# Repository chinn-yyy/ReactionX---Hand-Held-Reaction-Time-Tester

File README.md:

# ReactionX---Hand-Held-Reaction-Time-Tester
Ever wanted to know your reaction time? Well look no further because this is a reaction time tester! Simply click the button and wait for the red light to turn green.

I was doing some math in class and this kid next to me was on this reaction time tester website. I thought to myself, "could I make that in real life?" As soon as I got home I started researching, now I'm here. When you plug it in, it immediately greets you by saying, "ReactionX" and the highscore. Click start to test. Wait about 3-7 seconds before the LEDs turn from red to green. Once they do click either of the big buttons and it shows how long it took. Click early? Nope! When you click early it greets you with the screen of death, "To early!" 

I designed this as a project for Blueprint by HackClub and I think it turned out great. I used KiCad and Fusion360 to create all of the 3D models and electrical stuff. In total, this project took me about 5-6 hours.

Finally, here are some pictures of the finished result:

Fully Assembled (CAD):

Schematic:

PCB editor:

CAD:

BOM:

| Name:                          | Description:                                                        | $: (each) | Shipping $:                 | Ct: | Manufacturer: | Total $ (w/ tax + shipping): | URL:                                                                                                                                                                                                                                                                                                                                                                                                                                                                                                                                                                                                                                                                  |
|--------------------------------|---------------------------------------------------------------------|-----------|-----------------------------|-----|---------------|------------------------------|-----------------------------------------------------------------------------------------------------------------------------------------------------------------------------------------------------------------------------------------------------------------------------------------------------------------------------------------------------------------------------------------------------------------------------------------------------------------------------------------------------------------------------------------------------------------------------------------------------------------------------------------------------------------------|
| Seeed Studio XIAO RP2040       | Brains of the project, the MCU.                                     | $7.64     | $0.00                       | 1   | AliExpress    | $8.82                        | https://www.aliexpress.us/item/3256807240972277.html?spm=a2g0o.productlist.main.3.5d4a379crVwXcr&algo_pvid=40b24cbb-ccf1-49c9-b14e-7b9223d0d998&algo_exp_id=40b24cbb-ccf1-49c9-b14e-7b9223d0d998-2&pdp_ext_f=%7B%22order%22%3A%2234%22%2C%22eval%22%3A%221%22%2C%22fromPage%22%3A%22search%22%7D&pdp_npi=6%40dis%21USD%217.64%217.64%21%21%217.64%217.64%21%402101c44f17720601246066455e8d6c%2112000040716641980%21sea%21US%216916366760%21X%211%210%21n_tag%3A-29913%3Bd%3A729337c7%3Bm03_new_user%3A-29895&curPageLogUid=Ddu9g5fCrdZE&utparam-url=scene%3Asearch%7Cquery_from%3A%7Cx_object_id%3A1005007427287029%7C_p_origin_prod%3A                               |
| 6x6x6 Tacticle Push Button 12V | 2 pin buttons for clicking. Pack of 20.                             | $1.05     | $0.00                       | 1   | AliExpress    | $1.21                        | https://www.aliexpress.us/item/3256805859865632.html?spm=a2g0o.productlist.main.5.6d74378dUMKjkO&algo_pvid=602265cd-c18e-4c92-9666-59a2cdb82617&algo_exp_id=602265cd-c18e-4c92-9666-59a2cdb82617-4&pdp_ext_f=%7B%22order%22%3A%227215%22%2C%22eval%22%3A%221%22%2C%22fromPage%22%3A%22search%22%7D&pdp_npi=6%40dis%21USD%211.07%211.05%21%21%211.07%211.05%21%40210328db17714519752192151e5a1b%2112000035472972531%21sea%21US%216916366760%21X%211%210%21n_tag%3A-29913%3Bd%3A729337c7%3Bm03_new_user%3A-29895&curPageLogUid=KOWyfwiLLwPj&utparam-url=scene%3Asearch%7Cquery_from%3A%7Cx_object_id%3A1005006046180384%7C_p_origin_prod%3A                             |
| 0.91 inch OLED                 | 0.91 inch, 128x32, SSD1306, I2C, OLED display.                      | $1.97     | $0.00                       | 1   | AliExpress    | $2.27                        | https://www.aliexpress.us/item/3256805114690528.html?spm=a2g0o.productlist.main.33.508byZ3oyZ3oyT&algo_pvid=eb5a6790-e38d-4eb1-b34e-9abb2a502be0&algo_exp_id=eb5a6790-e38d-4eb1-b34e-9abb2a502be0-32&pdp_ext_f=%7B%22order%22%3A%222979%22%2C%22eval%22%3A%221%22%2C%22fromPage%22%3A%22search%22%7D&pdp_npi=6%40dis%21USD%211.97%211.97%21%21%211.97%211.97%21%402103212317713684409616193ef62c%2112000032548039884%21sea%21US%216916366760%21X%211%210%21n_tag%3A-29913%3Bd%3A729337c7%3Bm03_new_user%3A-29895&curPageLogUid=xd4wKAHaNW7A&utparam-url=scene%3Asearch%7Cquery_from%3A%7Cx_object_id%3A1005005301005280%7C_p_origin_prod%3A                           |
| SK6812 MINI-E RGB              | Addressable LEDs to tell you when to click the buttons. Pack of 20. | $2.37     | $0.00                       | 1   | AliExpress    | $2.73                        | https://www.aliexpress.us/item/3256805007401420.html?spm=a2g0o.productlist.main.5.277b37378ad11X&algo_pvid=1e78fde7-5114-430b-8e2b-01034e21220c&algo_exp_id=1e78fde7-5114-430b-8e2b-01034e21220c-4&pdp_ext_f=%7B%22order%22%3A%22354%22%2C%22eval%22%3A%221%22%2C%22fromPage%22%3A%22search%22%7D&pdp_npi=6%40dis%21USD%216.40%216.02%21%21%2143.95%2141.34%21%40210328df17716245048521216e488d%2112000032072424635%21sea%21US%216916366760%21X%211%210%21n_tag%3A-29913%3Bd%3A729337c7%3Bm03_new_user%3A-29895%3BpisId%3A5000000200978327&curPageLogUid=NBaz6TRdqNda&utparam-url=scene%3Asearch%7Cquery_from%3A%7Cx_object_id%3A1005005193716172%7C_p_origin_prod%3A |
| PCB                            | Custom printed circuit board. Pack of 5.                            | $6.60     | $3.30                       | 1   | JLCPCB        | $10.92                       | https://www.jlcpcb.com                                                                                                                                                                                                                                                                                                                                                                                                                                                                                                                                                                                                                                                |
| TOTAL:                         |                                                                     |           | *Ships with switching diode |     |               | $25.95                       | Link to Spreadsheet: https://docs.google.com/spreadsheets/d/1idejGBRncEobSxDtzh-fEDHo9kf2D_G95gO1wz3TeUY/edit?gid=0#gid=0                                                                                                                                                                                                                                                                                                                                                                                                                                                                                                                                             |

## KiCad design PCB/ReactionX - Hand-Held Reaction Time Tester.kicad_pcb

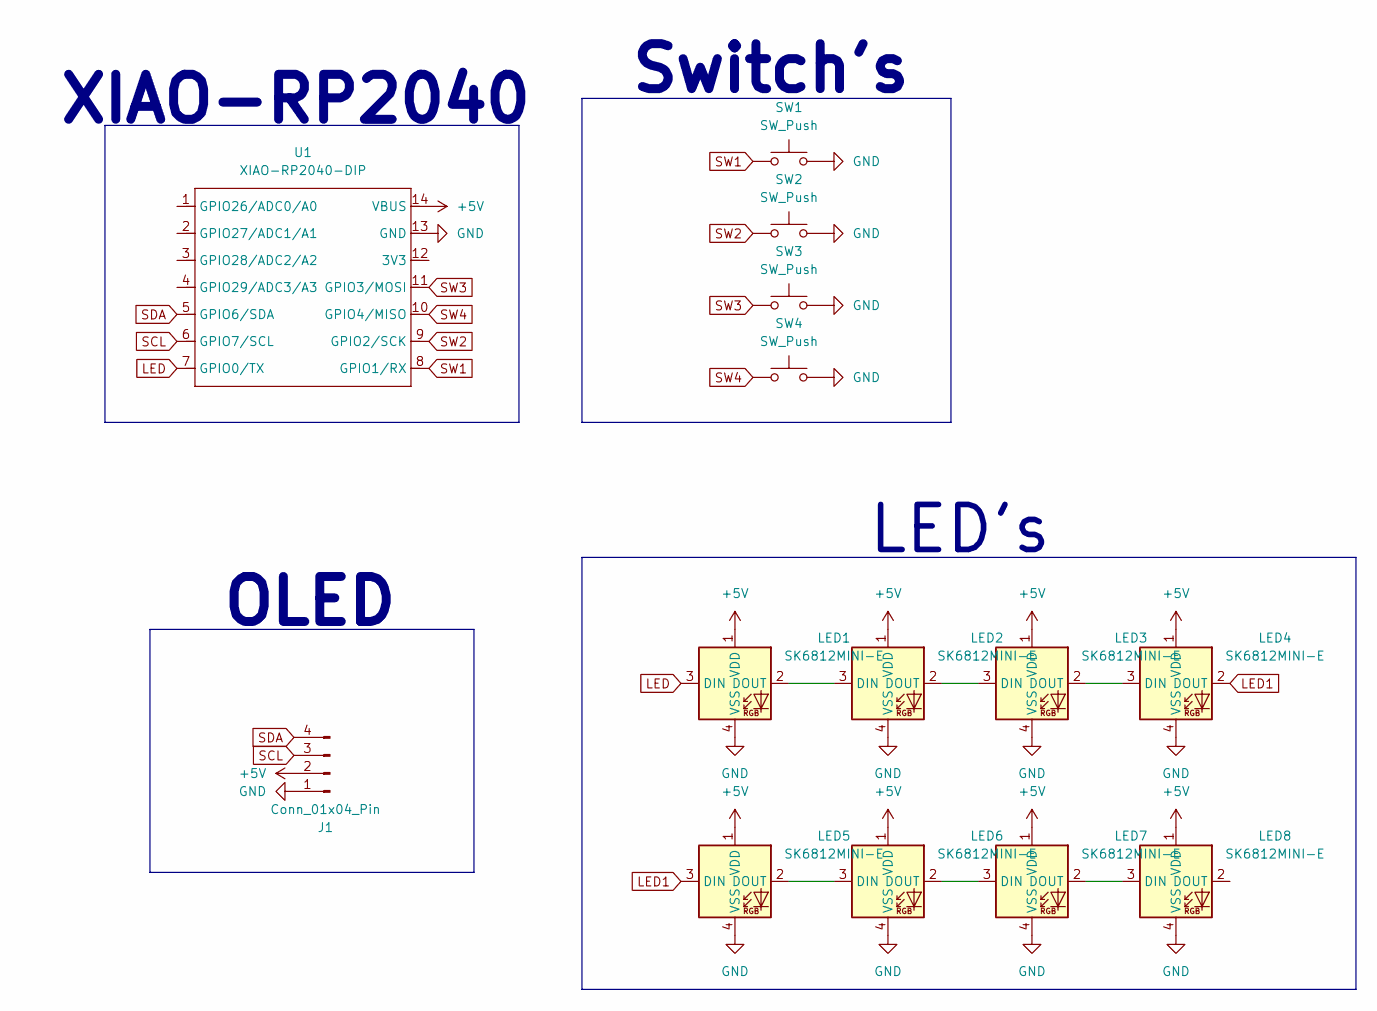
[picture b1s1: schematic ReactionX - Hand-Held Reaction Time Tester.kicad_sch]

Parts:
J1: Conn_01x04_Pin; OLED_0.91_128x32
LED1, LED2, LED3, LED4, LED5, LED6, LED7, LED8: SK6812MINI-E; LED_6028R
SW1, SW2, SW3, SW4: SW_Push; SW_PUSH_6mm_H7.3mm
U1: XIAO-RP2040-DIP

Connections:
+5V: J1.2, LED1.1 (VDD), LED2.1 (VDD), LED3.1 (VDD), LED4.1 (VDD), LED5.1 (VDD), LED6.1 (VDD), LED7.1 (VDD), LED8.1 (VDD), U1.14 (VBUS)
GND: J1.1, LED1.4 (VSS), LED2.4 (VSS), LED3.4 (VSS), LED4.4 (VSS), LED5.4 (VSS), LED6.4 (VSS), LED7.4 (VSS), LED8.4 (VSS), SW1.2, SW2.2, SW3.2, SW4.2, U1.13 (GND)
LED: LED1.3 (DIN), U1.7 (GPIO0/TX)
LED1: LED4.2 (DOUT), LED5.3 (DIN)
unnamed: LED1.2 (DOUT), LED2.3 (DIN)
unnamed: LED2.2 (DOUT), LED3.3 (DIN)
unnamed: LED3.2 (DOUT), LED4.3 (DIN)
unnamed: LED5.2 (DOUT), LED6.3 (DIN)
unnamed: LED6.2 (DOUT), LED7.3 (DIN)
unnamed: LED7.2 (DOUT), LED8.3 (DIN)
SCL: J1.3, U1.6 (GPIO7/SCL)
SDA: J1.4, U1.5 (GPIO6/SDA)
SW1: SW1.1, U1.8 (GPIO1/RX)
SW2: SW2.1, U1.9 (GPIO2/SCK)
SW3: SW3.1, U1.11 (GPIO3/MOSI)
SW4: SW4.1, U1.10 (GPIO4/MISO)

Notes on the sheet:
OLED
XIAO-RP2040
LED's
Switch's

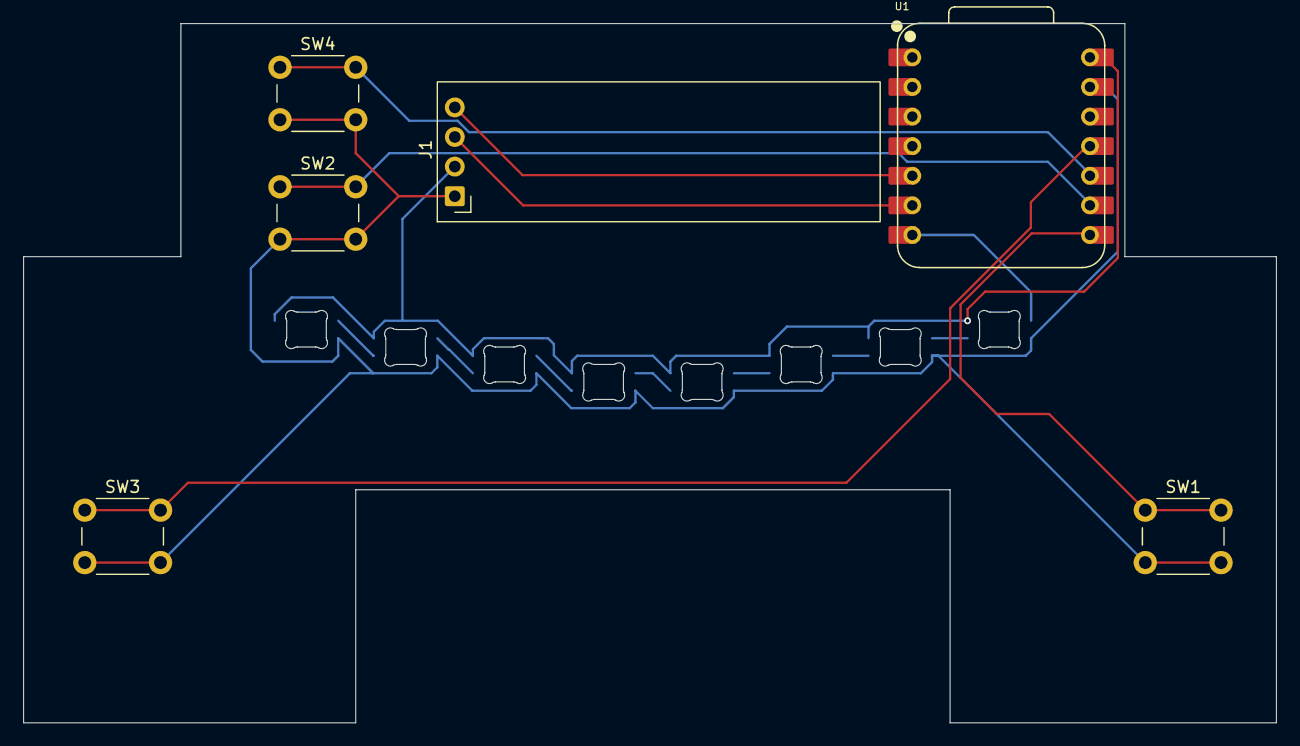
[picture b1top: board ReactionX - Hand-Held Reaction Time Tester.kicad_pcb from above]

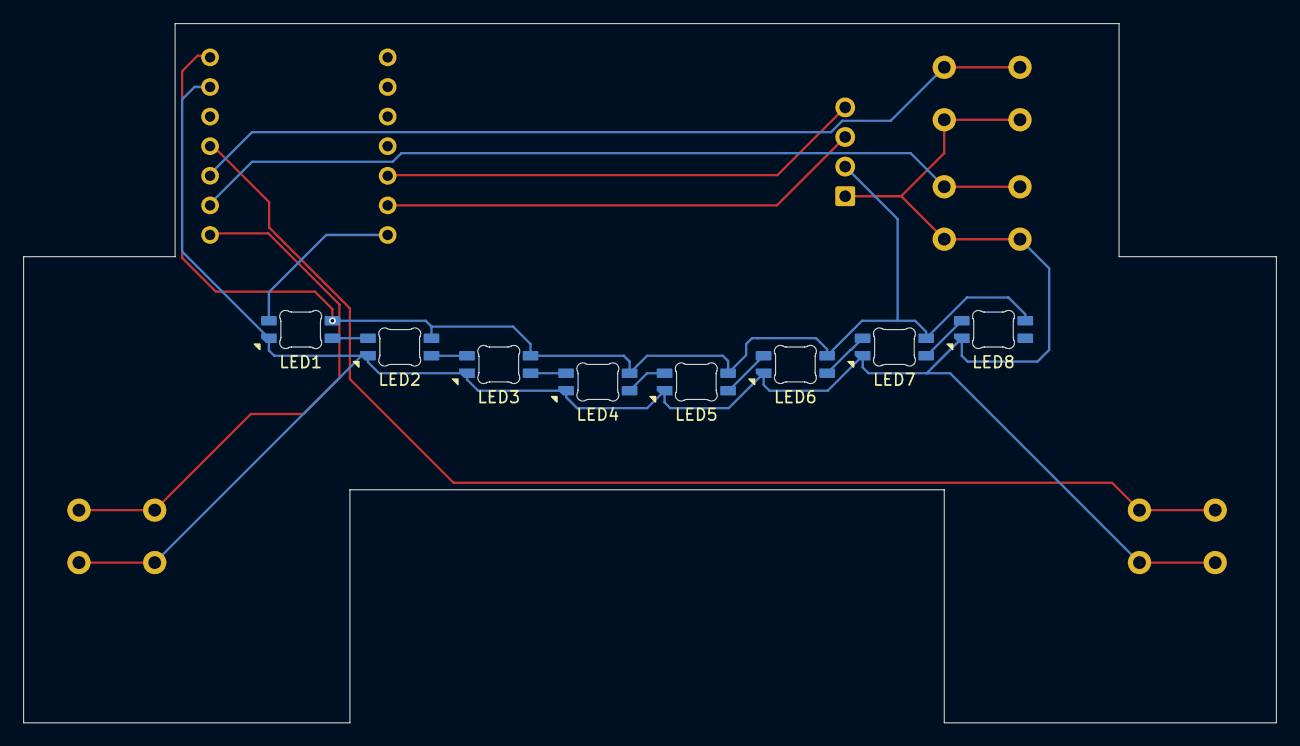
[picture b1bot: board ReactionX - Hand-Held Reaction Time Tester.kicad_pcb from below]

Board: 2 copper layers, 107.5 x 60.0 mm, 14 parts (8 on the bottom side), 16 nets.

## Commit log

2026-02-25 Create PLACEHOLDER
